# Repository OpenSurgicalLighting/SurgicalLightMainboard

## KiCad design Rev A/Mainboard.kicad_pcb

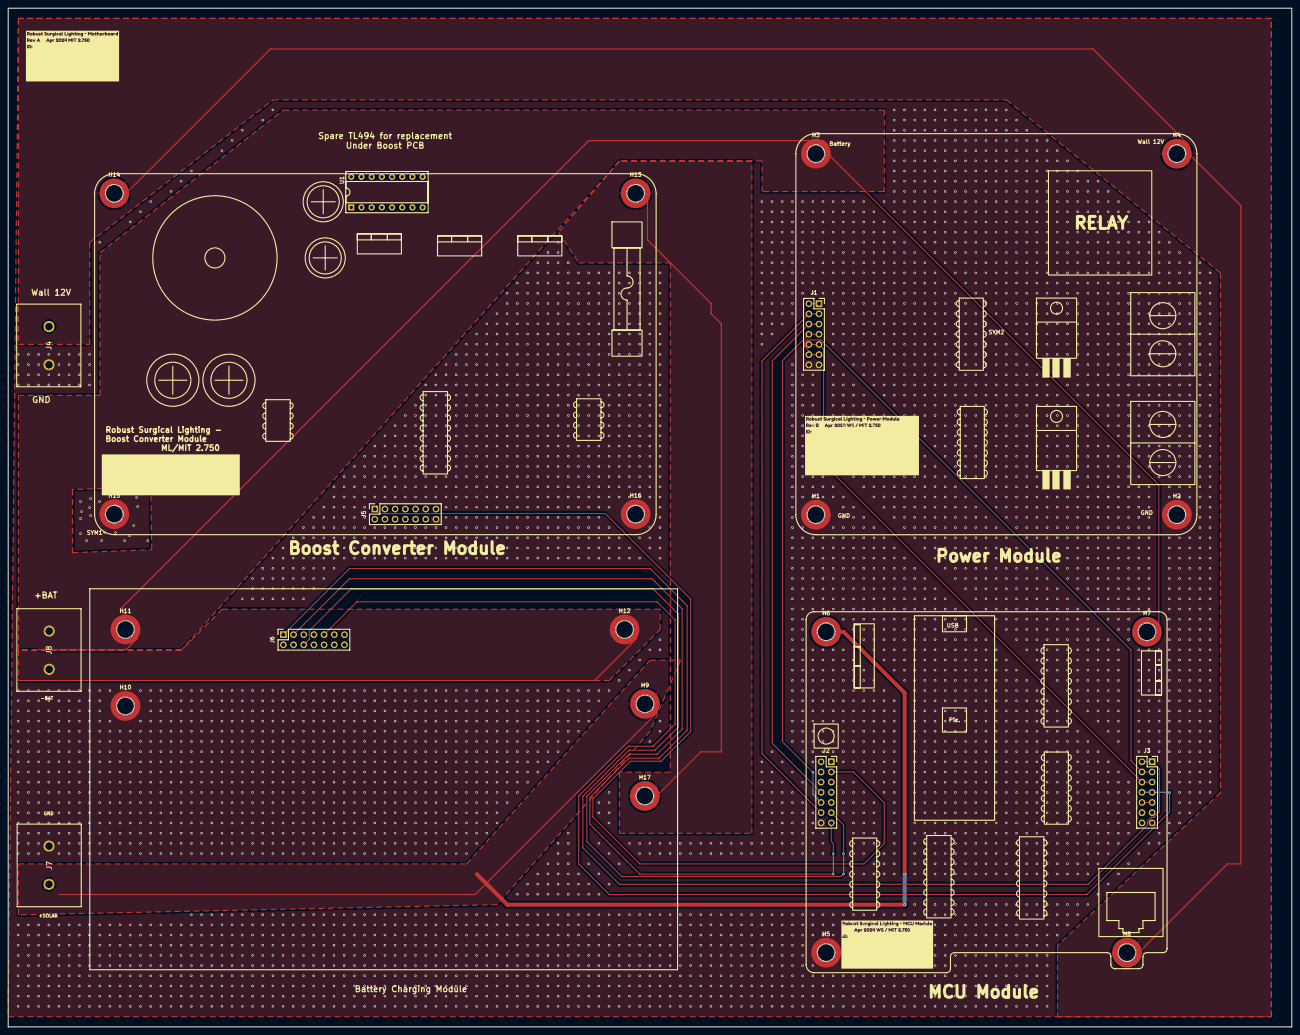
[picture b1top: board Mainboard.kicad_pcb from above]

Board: 2 copper layers, 320.0 x 254.0 mm, 31 parts (0 on the bottom side), 17 nets.

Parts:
H1, H2, H3, H4, H5, H6, H7, H8, H9, H10, H11, H12, H13, H14, H15, H16, H17: M3x11 Standoff; Mounting_Wuerth_WA-SMSI-M3_H11mm_9774110360
J1, J2, J3, J5, J6: 2x7 P2.54mm; PinSocket_2x07_P2.54mm_Vertical
J4, J7, J8: NC6-P108-02
SYM1: SYM_Hot_Small; BoostModule
SYM2: SYM_Hot_Small; PowerModule
SYM3: SYM_Hot_Small; MCUModule
U1: TL494; DIP-16_W7.62mm_Socket
kibuzzard-662C5ACC: G***; kibuzzard-662C5ACC
kibuzzard-662287CC: G***; kibuzzard-662287CC

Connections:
+12V: H4.1, H8.1, H14.1, J4.1
+24V: H13.1, H17.1
/BSTEna: J2.3, J5.1
/ISen1: J1.9, J1.10, J3.5, J3.6
/ISen2: J1.11, J1.12, J3.3, J3.4
/ISenBatChg: J3.1, J3.2, J6.6
/MCU With Multiplexers/SolarSense: J3.9, J3.10
/PWM1: J1.5, J1.6, J2.8
/PWM2: J1.7, J1.8, J2.10
/Relay: J1.3, J1.4, J2.12
/SolarSense: J3.7, J3.8, J6.9
BAT+: H3.1, H7.1, H11.1, J8.1
BAT-: H12.1, J8.2
GND: H1.1, H2.1, H5.1, H10.1, H15.1, H16.1, J1.13, J1.14, J2.14, J4.2, J5.14, J7.2
IRef: J2.11, J6.3
SOLAR+: H6.1, H9.1, J7.1
VRef: J2.13, J6.1

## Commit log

2024-03-02 Created Initial Files
2024-03-09 started block diagram
2024-03-20 Added power Module, started layout
2024-03-20 Added rpi pico module
